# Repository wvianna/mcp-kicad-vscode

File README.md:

# KiCAD MCP para VS Code — mcp-kicad-vscode

Workspace que combina um **servidor MCP para automação de design de PCB com KiCad** e o **projeto de hardware** (placa de circuito impresso) desenvolvido com ele.

- **`KiCAD-MCP-Server/`** — Servidor MCP (Node.js/TypeScript + Python) que permite que assistentes de IA controlem o KiCad: criação de esquemáticos, layout de PCB, roteamento, DRC, exportação e integração com catálogos de componentes.
- **`project-kicad/`** — Projeto KiCad real: placa **seguidor de linhas** de 4 camadas (`seguidor_de_linhas_4camada2-2026-1`), com 97 footprints e 83 nets.

## Visão geral

O objetivo deste workspace é usar IA assistida para projetar, validar e preparar o projeto da PCB para fabricação. O servidor expõe as operações do KiCad como *tools* MCP (233 registradas), permitindo que um agente abra projetos, posicione componentes, roteie trilhas, crie zonas, rode DRC e exporte arquivos de fabricação — com o [Model Context Protocol](https://modelcontextprotocol.io/) (spec 2025-06-18).

Principais características:

- **233 ferramentas MCP** em 16 categorias (esquemático, PCB, roteamento, regras/DRC, exportação, bibliotecas, JLCPCB/DigiKey, freerouting etc.);
- **Fluxo de trabalho completo de esquemático**: criação, edição em lote, hierarquia, netlist, ERC;
- **Design de PCB**: componentes, trilhas, vias, zonas/pours, clearances, DRC, fotos 2D;
- **Integração com fabricantes**: catálogo JLCPCB (2,5 M+ peças), datasheets via LCSC e busca DigiKey;
- **Autorouter Freerouting** integrado;
- **Suporte multiplataforma** (Linux, Windows, macOS);
- **Integração em tempo real com a UI do KiCad via IPC API** (experimental — exige `kicad-python`);
- Repositório upstream: [mixelpixx/KiCAD-MCP-Server](https://github.com/mixelpixx/KiCAD-MCP-Server) (detalhes completos no [README do servidor](KiCAD-MCP-Server/README.md)).

## Demonstração

Preview da placa do projeto:

Vídeo de preview da PCB (arquivo local — não incorporado diretamente):

[Preview da PCB seguidor de linhas](project-kicad/video/PREVIAPCBSEGUIDORLINHAS.mp4)

## Documentação acadêmica

Este workspace inclui dois documentos sobre o servidor MCP, de autoria de
**William da Silva Vianna (Instituto Federal Fluminense — IFF)**:

| Documento | PDF | Fontes LaTeX | Escopo |
|---|---|---|---|
| **Artigo** | [`artigo/artigo-mcp-kicad-vscode.pdf`](artigo/artigo-mcp-kicad-vscode.pdf) | [`artigo/`](artigo/) | 12 páginas: arquitetura, catálogo, resultados de teste, estudo de caso |
| **Monografia** | [`monografia/monografia-mcp-kicad-vscode.pdf`](monografia/monografia-mcp-kicad-vscode.pdf) | [`monografia/`](monografia/) | 56 páginas: detalhamento completo do MCP (arquitetura, 233 ferramentas, integrações, estudo de caso, apêndices) |

Os documentos citam apenas dados verificáveis do repositório. As evidências
(logs de teste de 10/09/2026 e relatório de DRC) estão em
[`evidencias/`](evidencias/); informações ausentes no workspace estão marcadas
explicitamente (ver [`monografia/MONOGRAFIA_PENDENCIAS.md`](monografia/MONOGRAFIA_PENDENCIAS.md)).

## Funcionalidades

### Servidor MCP (KiCAD-MCP-Server)

- [x] 233 tools MCP registradas + descoberta por palavra-chave (`search_tools`, `get_category_tools`)
- [x] Recursos dinâmicos (23) expondo o estado do projeto
- [x] Ferramentas de esquemático: componentes, wires, labels, hierarquia, ERC, netlist, sync PCB↔esquemático
- [x] Ferramentas de PCB: board, camadas, componentes, roteamento, vias, zonas, DRC, import/export
- [x] Criação de footprints e símbolos personalizados
- [x] Integração JLCPCB (busca local + API), datasheets LCSC e DigiKey
- [x] Roteador Freerouting (via Java, Docker ou Podman)
- [x] Suporte a importação de PCBs de fornecedores (PADS, Altium, Eagle, Allegro etc.)
- [ ] Backend IPC em tempo real — experimental, exige `kicad-python` (padrão atual local: SWIG)

### Projeto de hardware (project-kicad)

- [x] Placa 4 camadas (F.Cu, B.Cu, In1.Cu, In2.Cu) — 82,2 × 80,3 mm
- [x] 97 componentes (80 da lib `mylib`, sensores IR `ITR8307`, ESP32, ponte H, MPPT, USB-C — conforme nets e BOM)
- [x] 83 nets (GND, +5V, +3V3, VBAT e sinais `/mptt/*`, `/ponteH/*`, `/usb-c/*`, `/IO*`)
- [x] DRC executado via `kicad-cli` (10/09/2026): 11 violações residuais (9 erros + 2 avisos), **0 itens não conectados** — relatório em [`project-kicad/docs/drc-seguidor-de-linhas-2026-09-10.json`](project-kicad/docs/drc-seguidor-de-linhas-2026-09-10.json); correções pendentes antes da fabricação
- [x] `BOM.csv` e bibliotecas locais (`mylib/`, `logopcb/`)

## Arquitetura

```mermaid
flowchart LR
    A[Assistente de IA<br/>cliente MCP] -->|stdio| B[KiCAD-MCP-Server<br/>Node.js / TypeScript]
    B -->|comandos JSON| C[python/kicad_interface.py<br/>SWIG pcbnew]
    B -.->|IPC opcional| D[KiCad IPC API<br/>exige kicad-python]
    C --> E[Arquivos .kicad_pro/.kicad_pcb/.kicad_sch]
    D --> E
    E --> F[project-kicad/<br/>seguidor_de_linhas_4camada2-2026-1]
    C --> G[kicad-cli<br/>DRC / exportações]
```

Fluxo: o agente de IA envia chamadas de ferramenta ao servidor Node; o servidor despacha para o processo Python que opera o KiCad via `pcbnew` (SWIG) — ou pela IPC API quando disponível — e os resultados refletem nos arquivos do projeto KiCad.

## Estrutura do projeto

```text
mcp-kicad-vscode/
├── KiCAD-MCP-Server/          # Servidor MCP (repo aninhado, upstream mixelpixx)
│   ├── src/                   # TypeScript — servidor e 233 tools
│   ├── python/                # Interface pcbnew (SWIG) / IPC
│   ├── tests/                 # testes pytest (test_*.py)
│   ├── tests-ts/              # testes Vitest (*.test.ts)
│   ├── config/                # exemplos de configuração de clientes MCP
│   ├── docs/                  # documentação detalhada do servidor
│   ├── package.json           # scripts de build/test/lint
│   ├── pyproject.toml         # Black/Isort/MyPy
│   └── run-kicad-mcp.sh       # launcher com env do KiCad (snap)
├── project-kicad/             # Projeto de hardware (PCB)
│   ├── seguidor_de_linhas_4camada2-2026-1.kicad_pro/.kicad_pcb/.kicad_sch
│   ├── mylib/                 # bibliotecas de footprints locais
│   ├── imagens/               # imagens da placa
│   ├── video/                 # vídeo de preview
│   ├── docs/                  # PDF do esquemático e listagens
│   └── BOM.csv
├── docs/                      # guias de setup local (pt-BR)
└── .gitignore
```

## Requisitos

### Software

| Ferramenta | Versão | Observação |
|---|---|---|
| Node.js | ≥ 20 | usado no CI (20.x/22.x) |
| TypeScript | 5.9 | compilação via `npm run build` |
| npm | — | gerenciador de dependências |
| Python | ≥ 3.9 | local: 3.12.3 (`.venv`) |
| KiCad | 9.0.7 | instalação **snap** (`/snap/kicad/22`) |
| JRE | 21 | apenas para suítes de teste do Freerouting (CI) |

Opcional: `kicad-python` (`pip install kicad-python`) habilita o backend IPC em tempo real; sem ele o servidor usa o backend SWIG.

### Hardware

- Para executar o servidor: computador com o KiCad instalado (o próprio KiCad é o "hardware").
- Projeto `project-kicad`: placa 4 camadas (ver [BOM.csv](project-kicad/BOM.csv) e [esquemático](project-kicad/docs/esquemático) para lista completa de componentes).

## Instalação

### 1. Clonar e preparar o servidor

```bash
cd KiCAD-MCP-Server
npm ci
npm run build
```

### 2. Ambiente Python

```bash
cd KiCAD-MCP-Server
python -m venv .venv
source .venv/bin/activate
pip install -r requirements.txt -r requirements-dev.txt
```

### 3. KiCad (snap) e habilitação da IPC API

Instale o KiCad 9 via snap e, no KiCad, habilite a API IPC em:

**Preferences → Plugins → Enable IPC API Server**

> Passo a passo completo de instalação local em [`docs/setup-mcp.txt`](docs/setup-mcp.txt).

## Configuração

### Variáveis de ambiente (opcional)

Copie [`.env.example`](KiCAD-MCP-Server/.env.example) para `.env` para habilitar integrações com JLCPCB e DigiKey:

```bash
cp KiCAD-MCP-Server/.env.example KiCAD-MCP-Server/.env
```

- `JLCPCB_APP_ID`, `JLCPCB_API_KEY`, `JLCPCB_API_SECRET` — API da JLCPCB (opcional; sem elas, a busca usa a base local);
- `DIGIKEY_CLIENT_ID`, `DIGIKEY_CLIENT_SECRET`, `DIGIKEY_LOCALE_*` — API DigiKey (opcional).

**Nunca commite o `.env`** — valores reais não devem aparecer em exemplos ou commits.

### Configuração do cliente MCP

Exemplos para diferentes clientes em `KiCAD-MCP-Server/config/`:

- `claude-desktop-config.json`, `opencode.json`, `vscode-mcp.example.json`
- `linux-config.example.json`, `macos-config.example.json`, `windows-config.example.json`

Variáveis de ambiente relevantes (definidas em `.vscode/mcp.json` — caminhos **máquina-específicos**, ajuste conforme sua instalação):

| Variável | Efeito |
|---|---|
| `KICAD_BACKEND=auto` | tenta IPC e cai para SWIG se `kicad-python` não estiver instalado |
| `KICAD_PYTHON` | caminho do interpretador Python do servidor (venv) |
| `PYTHONPATH` | `pcbnew` do KiCad (snap) |
| `LD_LIBRARY_PATH` | bibliotecas nativas do KiCad (snap) — obrigatório |
| `KICAD_AUTO_LAUNCH=false` | não abre o KiCad automaticamente |

## Uso

### Iniciar o servidor MCP

No VS Code: **Ctrl+Shift+P → `MCP: Start Server`** (usa `.vscode/mcp.json`).

Ou pelo terminal:

```bash
cd KiCAD-MCP-Server
./run-kicad-mcp.sh          # launcher com env do KiCad snap
# equivale a:
node dist/index.js          # sem env do KiCad: SWIG/headless
```

### Exemplos de fluxo com o assistente de IA

Com o servidor MCP ativo, um assistente pode, por exemplo:

1. `open_project` no `project-kicad/seguidor_de_linhas_4camada2-2026-1.kicad_pro`;
2. `get_board_info` / `get_component_list` para inspecionar a placa;
3. `run_drc` para validar regras de projeto;
4. `export_gerber` / `export_drill` para gerar arquivos de fabricação.

Todos os comandos de ferramentas MCP estão documentados em `KiCAD-MCP-Server/docs/TOOL_INVENTORY.md`.

### Trabalhando com o projeto KiCad

Abrir o projeto no KiCad e/ou validar DRC pela linha de comando (com o ambiente do snap exportado):

```bash
cd project-kicad
kicad-cli pcb drc --output /tmp/drc.json --format json seguidor_de_linhas_4camada2-2026-1.kicad_pcb
```

## Solução de problemas

| Sintoma | Causa provável | Solução |
|---|---|---|
| `ImportError: libwx_gtk3u_gl-3.2.so.0` | `LD_LIBRARY_PATH` ausente | Usar `./run-kicad-mcp.sh` ou exportar as variáveis do snap |
| `No module named 'pcbnew'` | `PYTHONPATH` errado | `export PYTHONPATH=/snap/kicad/22/usr/lib/python3/dist-packages` |
| Servidor em `backend: swig`, sem realtime | `kicad-python` não instalado | `pip install kicad-python` (ou aceitar SWIG) |
| `kicad-cli: error while loading shared libraries: libkicommon.so` | env do snap ausente | Exportar `LD_LIBRARY_PATH` antes do `kicad-cli` |
| DRC acusa clearance de zona | fill de zona desatualizado | Refill das zonas (tecla **B** no KiCad ou `pcbnew.ZONE_FILLER`) |
| `docs/TOOL_INVENTORY.md` desatualizado | tools adicionadas/removidas | `npm run docs:tools` |

## Desenvolvimento

```bash
cd KiCAD-MCP-Server

npm run build           # compilar TypeScript -> dist/
npm run dev             # watch + nodemon (redeployment automático)
npm run lint            # eslint src/ + black --check + mypy + flake8 (python/)
npm run format          # prettier 'src/**/*.ts' && black python/
npm run test            # vitest (tests-ts/) + pytest (tests/)
npm run test:ts         # somente testes TypeScript
npm run test:py         # somente testes Python
npm run test:coverage   # pytest com cobertura (pytest-cov)
npm run docs:tools      # regenerar docs/TOOL_INVENTORY.md
pre-commit run --all-files   # hooks de qualidade (git)
```

- **Testes**: Vitest (`tests-ts/*.test.ts`) e pytest (`tests/test_*.py`, `testpaths = tests`).
- **CI**: `.github/workflows/ci.yml` (matrix Node 20/22 e Python 3.9–3.12) — inclui gates de `docs:tools:check` e `lint:ts`.
- **Estilo (em `KiCAD-MCP-Server/`):** TypeScript estrito + Prettier/ESLint; Python Black (100 col) + Isort + MyPy + Flake8.

## Licença

- **KiCAD-MCP-Server:** MIT (ver [`LICENSE`](KiCAD-MCP-Server/LICENSE)).
- **Workspace/projeto raiz:** licença não identificada — nenhum arquivo `LICENSE` foi encontrado na raiz deste repositório.

## Créditos

- Servidor MCP: projeto upstream [KiCAD-MCP-Server](https://github.com/mixelpixx/KiCAD-MCP-Server) (autores originais conforme repositório; documentação detalhada em [`KiCAD-MCP-Server/README.md`](KiCAD-MCP-Server/README.md)).
- Projeto de hardware `seguidor_de_linhas_4camada2-2026-1`: o bloco de título do esquemático registra **"Autor: William / IFF"** (revisão `r01`), confirmando a autoria no próprio projeto.

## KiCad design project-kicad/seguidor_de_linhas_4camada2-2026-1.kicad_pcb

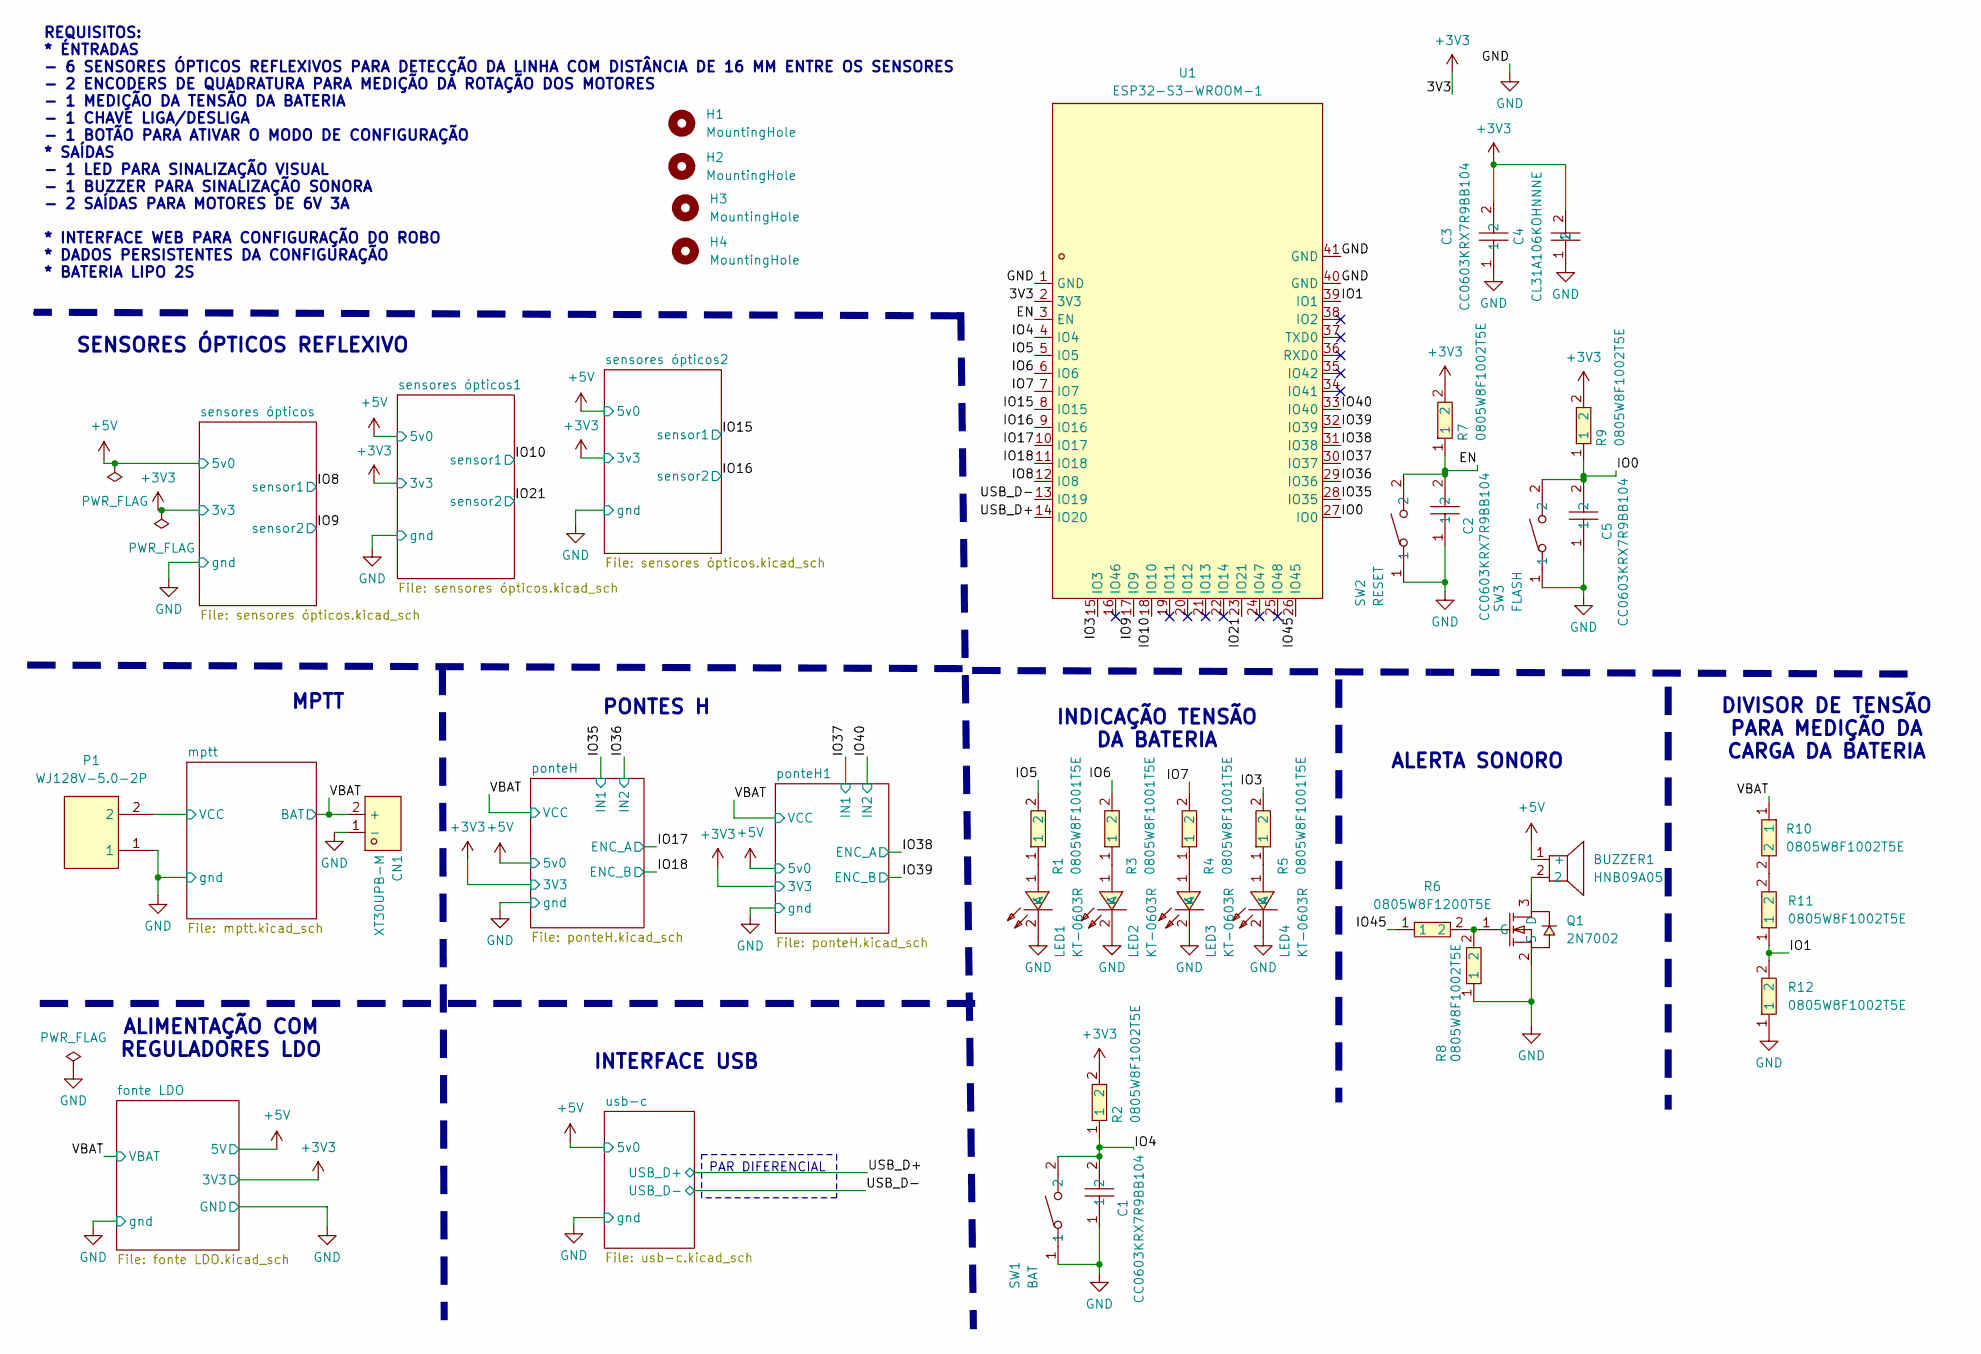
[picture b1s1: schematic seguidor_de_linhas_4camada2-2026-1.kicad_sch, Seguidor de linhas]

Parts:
BUZZER1: HNB09A05; BUZ-TH_BD9.6-P5.00-D0.7-FD; MPN HNB09A05; LCSC Part C96493
C1, C2, C3, C5: CC0603KRX7R9BB104; C0603; MPN CC0603KRX7R9BB104; LCSC Part C14663
C4: CL31A106KOHNNNE; C1206; MPN CL31A106KOHNNNE; LCSC Part C1849
CN1: XT30UPB-M; CONN-TH_XT30UPB-M; MPN XT30UPB-M; LCSC Part C428721
H1, H2, H3, H4: MountingHole; MountingHole_3.2mm_M3
LED1, LED2, LED3, LED4: KT-0603R; LED-SMD_L1.6-W0.8-R-RD; MPN KT-0603R; LCSC Part C2286
P1: WJ128V-5.0-2P; CONN-TH_2P-P5.00_WJ128V-5.0-2P; MPN WJ128V-5.0-02P-14-00A; LCSC Part C8269
Q1: 2N7002; SOT-23-3_L2.9-W1.3-P1.90-LS2.4-BR; MPN 2N7002; LCSC Part C8545
R1, R3, R4, R5: 0805W8F1001T5E; R0805; MPN 0805W8F1001T5E; LCSC Part C17513
R2, R7, R8, R9, R10, R11, R12: 0805W8F1002T5E; R0805; MPN 0805W8F1002T5E; LCSC Part C17414
R6: 0805W8F1200T5E; R0805; MPN 0805W8F1200T5E; LCSC Part C17437
SW1: BAT; SW-SMD_L3.9-W3.0-P4.45; MPN TS-1088-AR02016; LCSC Part C720477
SW2: RESET; SW-SMD_L3.9-W3.0-P4.45; MPN TS-1088-AR02016; LCSC Part C720477
SW3: FLASH; SW-SMD_L3.9-W3.0-P4.45; MPN TS-1088-AR02016; LCSC Part C720477
U1: ESP32-S3-WROOM-1; WIRELM-SMD_ESP32-S3-WROOM-1; MPN ESP32-S3-WROOM-1-N16R8; LCSC Part C2913202

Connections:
+3V3: C3.2, C4.2, R2.2, R7.2, R9.2, U1.2 (3V3); also elsewhere on the board
+5V: BUZZER1.1 (+); also elsewhere on the board
/EN: C2.2, R7.1, SW2.2, U1.3 (EN)
/IO0: C5.2, R9.1, SW3.2, U1.27 (IO0)
/IO1: R11.1, R12.2, U1.39 (IO1)
/IO3: R5.2, U1.15 (IO3)
/IO4: C1.2, R2.1, SW1.2, U1.4 (IO4)
/IO5: R1.2, U1.5 (IO5)
/IO6: R3.2, U1.6 (IO6)
/IO7: R4.2, U1.7 (IO7)
/IO8: U1.12 (IO8); also elsewhere on the board
/IO9: U1.17 (IO9); also elsewhere on the board
/IO10: U1.18 (IO10); also elsewhere on the board
/IO15: U1.8 (IO15); also elsewhere on the board
/IO16: U1.9 (IO16); also elsewhere on the board
/IO17: U1.10 (IO17); also elsewhere on the board
/IO18: U1.11 (IO18); also elsewhere on the board
/IO21: U1.23 (IO21); also elsewhere on the board
/IO35: U1.28 (IO35); also elsewhere on the board
/IO36: U1.29 (IO36); also elsewhere on the board
/IO37: U1.30 (IO37); also elsewhere on the board
/IO38: U1.31 (IO38); also elsewhere on the board
/IO39: U1.32 (IO39); also elsewhere on the board
/IO40: U1.33 (IO40); also elsewhere on the board
/IO45: R6.1, U1.26 (IO45)
/USB_D+: U1.14 (IO20); also elsewhere on the board
/USB_D-: U1.13 (IO19); also elsewhere on the board
/VBAT: CN1.2 (+), R10.1; also elsewhere on the board
/mptt/VCC: P1.2; also elsewhere on the board
GND: C1.1, C2.1, C3.1, C4.1, C5.1, CN1.1 (-), LED1.2 (K), LED2.2 (K), LED3.2 (K), LED4.2 (K), P1.1, Q1.2 (S), R8.1, R12.1, SW1.1, SW2.1, SW3.1, U1.1 (GND), U1.40 (GND), U1.41 (GND); also elsewhere on the board
unnamed: LED1.1 (A), R1.1
unnamed: LED2.1 (A), R3.1
unnamed: LED3.1 (A), R4.1
unnamed: LED4.1 (A), R5.1
unnamed: BUZZER1.2, Q1.3 (D)
unnamed: Q1.1 (G), R6.2, R8.2
unnamed: R10.2, R11.2

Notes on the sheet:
PONTES H
INTERFACE USB
INDICAÇÃO TENSÃO DA BATERIA
SENSORES ÓPTICOS REFLEXIVO
ALERTA SONORO
REQUISITOS: * ÉNTRADAS - 6 SENSORES ÓPTICOS REFLEXIVOS PARA DETECÇÃO DA LINHA COM DISTÂNCIA DE 16 MM ENTRE OS SENSORES - 2 ENCODERS DE QUADRATURA PARA MEDIÇÃO DA ROTAÇÃO DOS MOTORES - 1 MEDIÇÃO DA TENSÃO DA BATERIA - 1 CHAVE LIGA/DESLIGA - 1 BOTÃO PARA ATIVAR O MODO DE CONFIGURAÇÃO * SAÍDAS - 1 LED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
MPTT
DIVISOR DE TENSÃO PARA MEDIÇÃO DA CARGA DA BATERIA
ALIMENTAÇÃO COM REGULADORES LDO
PAR DIFERENCIAL

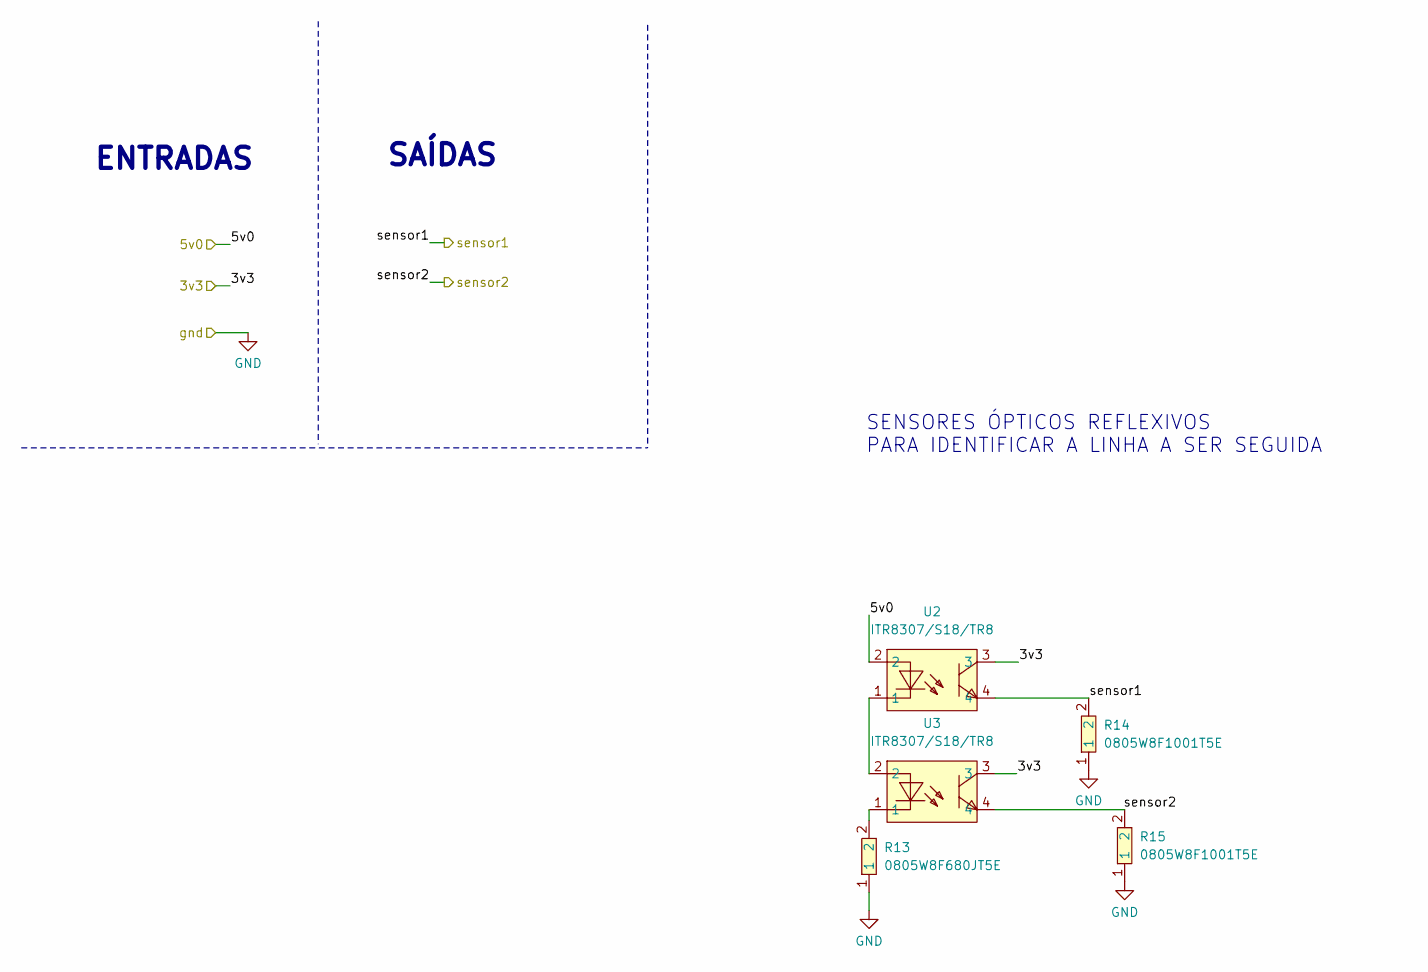
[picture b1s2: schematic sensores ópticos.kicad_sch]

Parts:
R13: 0805W8F680JT5E; R0805; MPN 0805W8F680JT5E; LCSC Part C17802
R14, R15: 0805W8F1001T5E; R0805; MPN 0805W8F1001T5E; LCSC Part C17513
U2, U3: ITR8307/S18/TR8; OPTO-SMD_ITR8307-S18-TR8-B; MPN ITR8307/S18/TR8(B); LCSC Part C115037

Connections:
+3V3: U2.3, U3.3; also elsewhere on the board
+5V: U2.2; also elsewhere on the board
/IO8: R14.2, U2.4; also elsewhere on the board
/IO9: R15.2, U3.4; also elsewhere on the board
GND: R13.1, R14.1, R15.1; also elsewhere on the board
unnamed: R13.2, U3.1
unnamed: U2.1, U3.2

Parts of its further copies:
R16, R19: 0805W8F680JT5E; R0805; MPN 0805W8F680JT5E; LCSC Part C17802
R17, R18, R20, R21: 0805W8F1001T5E; R0805; MPN 0805W8F1001T5E; LCSC Part C17513
U4, U5, U6, U7: ITR8307/S18/TR8; OPTO-SMD_ITR8307-S18-TR8-B; MPN ITR8307/S18/TR8(B); LCSC Part C115037

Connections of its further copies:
+3V3: U4.3, U5.3, U6.3, U7.3; also elsewhere on the board
+5V: U4.2, U6.2; also elsewhere on the board
/IO10: R17.2, U4.4; also elsewhere on the board
/IO15: R20.2, U6.4; also elsewhere on the board
/IO16: R21.2, U7.4; also elsewhere on the board
/IO21: R18.2, U5.4; also elsewhere on the board
GND: R16.1, R17.1, R18.1, R19.1, R20.1, R21.1; also elsewhere on the board
unnamed: R16.2, U5.1
unnamed: R19.2, U7.1
unnamed: U4.1, U5.2
unnamed: U6.1, U7.2

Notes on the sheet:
SENSORES ÓPTICOS REFLEXIVOS PARA IDENTIFICAR A LINHA A SER SEGUIDA
SAÍDAS
ENTRADAS

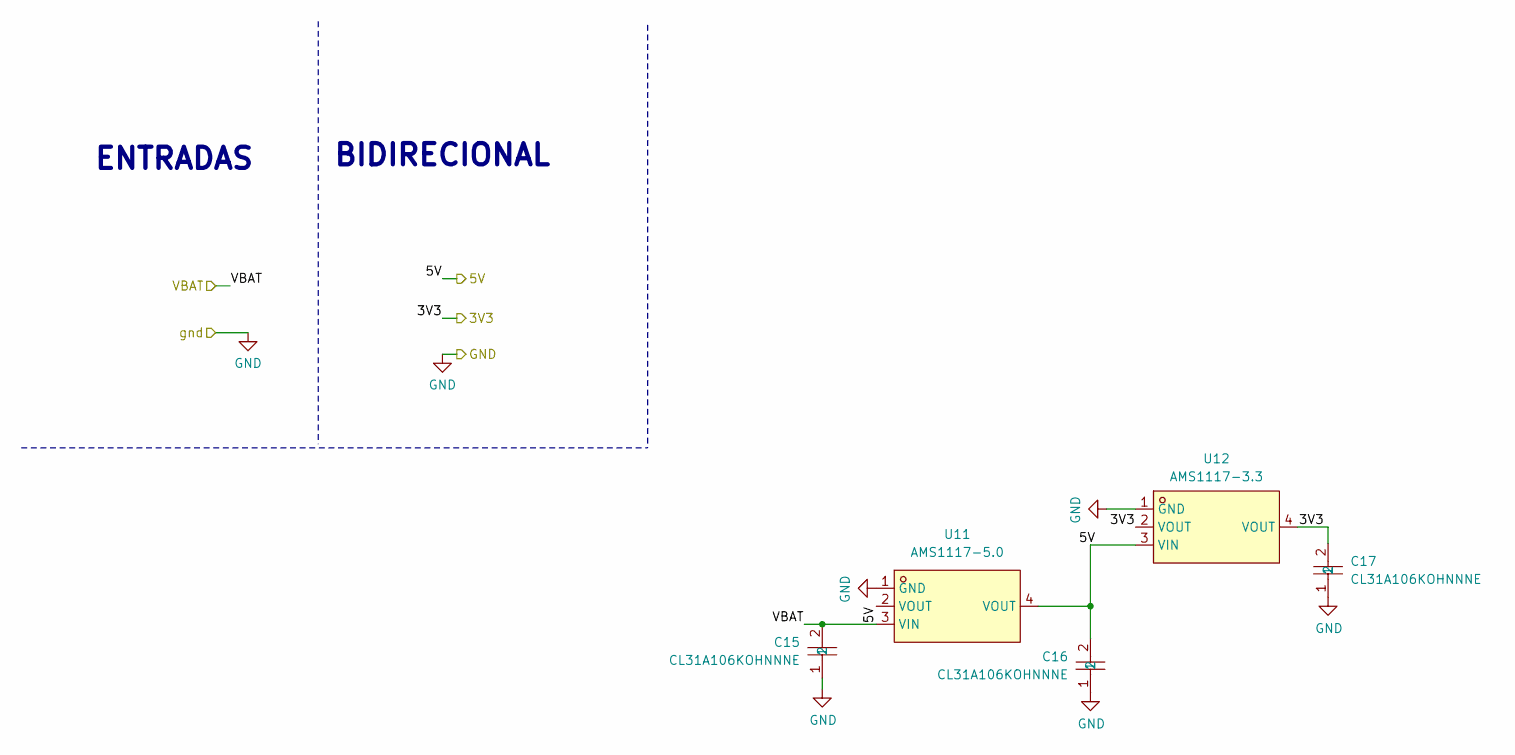
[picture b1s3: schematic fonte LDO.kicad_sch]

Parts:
C15, C16, C17: CL31A106KOHNNNE; C1206; MPN CL31A106KOHNNNE; LCSC Part C1849
U11: AMS1117-5.0; SOT-223_L6.5-W3.5-P2.30-LS7.0-BR; MPN AMS1117-5.0; LCSC Part C6187
U12: AMS1117-3.3; SOT-223-3_L6.5-W3.4-P2.30-LS7.0-BR; MPN AMS1117-3.3; LCSC Part C6186

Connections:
+3V3: C17.2, U12.2 (VOUT), U12.4 (VOUT); also elsewhere on the board
+5V: C16.2, U11.2 (VOUT), U11.4 (VOUT), U12.3 (VIN); also elsewhere on the board
/VBAT: C15.2, U11.3 (VIN); also elsewhere on the board
GND: C15.1, C16.1, C17.1, U11.1 (GND), U12.1 (GND); also elsewhere on the board

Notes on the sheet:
BIDIRECIONAL
ENTRADAS

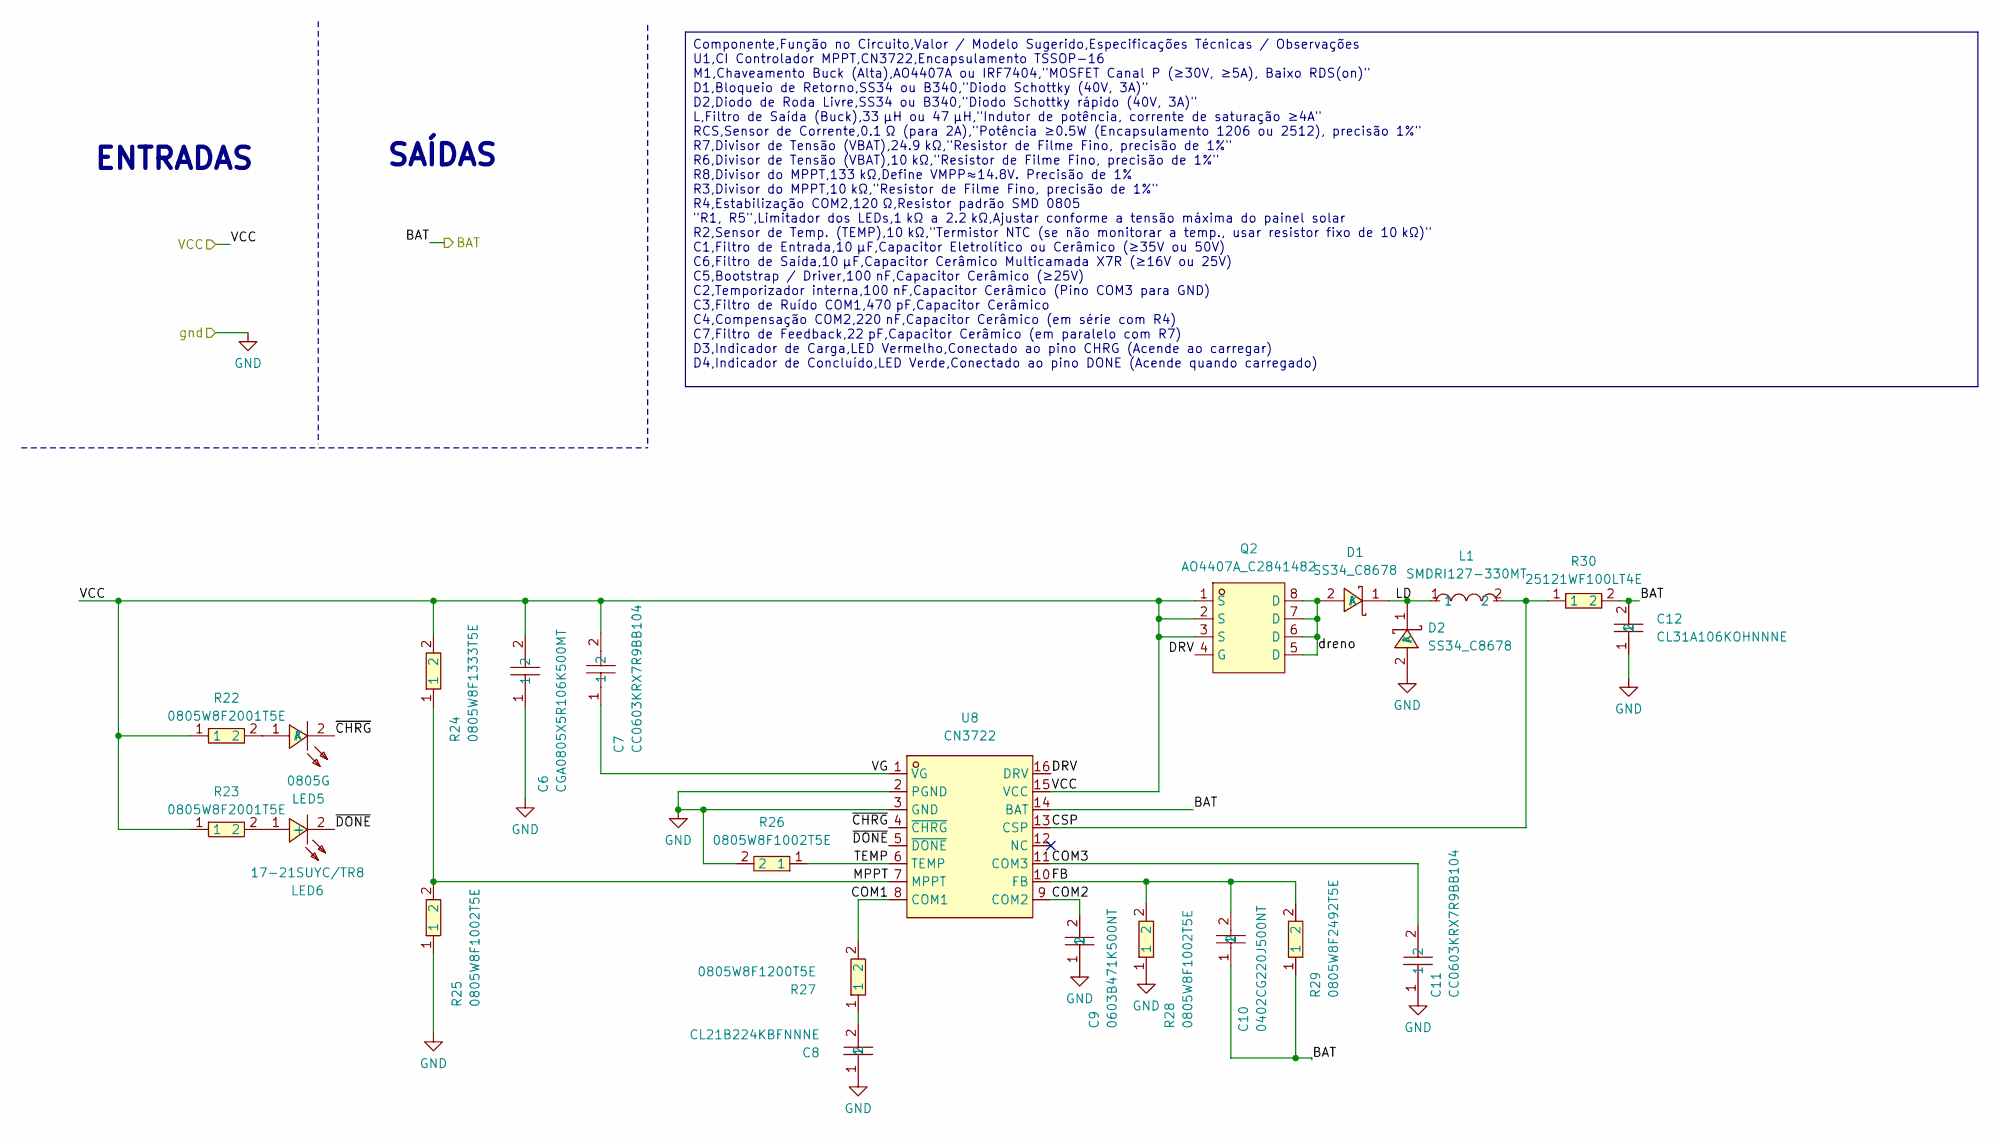
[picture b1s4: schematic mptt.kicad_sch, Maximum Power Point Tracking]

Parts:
C6: CGA0805X5R106K500MT; C0805; MPN CGA0805X5R106K500MT; LCSC Part C6119889
C7, C11: CC0603KRX7R9BB104; C0603; MPN CC0603KRX7R9BB104; LCSC Part C14663
C8: CL21B224KBFNNNE; C0805; MPN CL21B224KBFNNNE; LCSC Part C5378
C9: 0603B471K500NT; C0603; MPN 0603B471K500NT; LCSC Part C1620
C10: 0402CG220J500NT; C0402; MPN 0402CG220J500NT; LCSC Part C1555
C12: CL31A106KOHNNNE; C1206; MPN CL31A106KOHNNNE; LCSC Part C1849
D1, D2: SS34_C8678; SMA_L4.3-W2.6-LS5.2-RD; MPN SS34; LCSC Part C8678
L1: SMDRI127-330MT; IND-SMD_L12.3-W12.3; MPN SMDRI127-330MT; LCSC Part C9400
LED5: 0805G; LED0805-R-RD; MPN KT-0805G; LCSC Part C2297
LED6: 17-21SUYC/TR8; LED0805-R-RD; MPN KT-0805黄灯; LCSC Part C2296
Q2: AO4407A_C2841482; SOP-8_L5.0-W4.0-P1.27-LS6.0-BL; MPN AO4407A; LCSC Part C2841482
R22, R23: 0805W8F2001T5E; R0805; MPN 0805W8F2001T5E; LCSC Part C17604
R24: 0805W8F1333T5E; R0805; MPN 0805W8F1333T5E; LCSC Part C17452
R25, R26, R28: 0805W8F1002T5E; R0805; MPN 0805W8F1002T5E; LCSC Part C17414
R27: 0805W8F1200T5E; R0805; MPN 0805W8F1200T5E; LCSC Part C17437
R29: 0805W8F2492T5E; R0805; MPN 0805W8F2492T5E; LCSC Part C17571
R30: 25121WF100LT4E; R2512; MPN 25121WF100LT4E; LCSC Part C25466
U8: CN3722; TSSOP-16_L5.0-W4.4-P0.65-LS6.4-BL; MPN CN3722; LCSC Part C77905

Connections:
/VBAT: C10.1, C12.2, R29.1, R30.2, U8.14 (BAT); also elsewhere on the board
/mptt/COM1: R27.2, U8.8 (COM1)
/mptt/COM2: C9.2, U8.9 (COM2)
/mptt/COM3: C11.2, U8.11 (COM3)
/mptt/CSP: L1.2, R30.1, U8.13 (CSP)
/mptt/DRV: Q2.4 (G), U8.16 (DRV)
/mptt/FB: C10.2, R28.2, R29.2, U8.10 (FB)
/mptt/LD: D1.1 (K), D2.1 (K), L1.1
/mptt/MPPT: R24.1, R25.2, U8.7 (MPPT)
/mptt/TEMP: R26.1, U8.6 (TEMP)
/mptt/VCC: C6.2, C7.2, Q2.1 (S), Q2.2 (S), Q2.3 (S), R22.1, R23.1, R24.2, U8.15 (VCC); also elsewhere on the board
/mptt/VG: C7.1, U8.1 (VG)
/mptt/dreno: D1.2 (A), Q2.5 (D), Q2.6 (D), Q2.7 (D), Q2.8 (D)
/mptt/~CHRG: LED5.2 (K), U8.4 (~CHRG)
/mptt/~DONE: LED6.2 (-), U8.5 (~DONE)
GND: C6.1, C8.1, C9.1, C11.1, C12.1, D2.2 (A), R25.1, R26.2, R28.1, U8.2 (PGND), U8.3 (GND); also elsewhere on the board
unnamed: C8.2, R27.1
unnamed: LED5.1 (A), R22.2
unnamed: LED6.1 (+), R23.2

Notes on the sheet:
SAÍDAS
ENTRADAS
Componente,Função no Circuito,Valor / Modelo Sugerido,Especificações Técnicas / Observações U1,CI Controlador MPPT,CN3722,Encapsulamento TSSOP-16 M1,Chaveamento Buck (Alta),AO4407A ou IRF7404,"MOSFET Canal P (≥30V, ≥5A), Baixo RDS(on)​" D1,Bloqueio de Retorno,SS34 ou B340,"Diodo Schottky (40V, 3A)"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

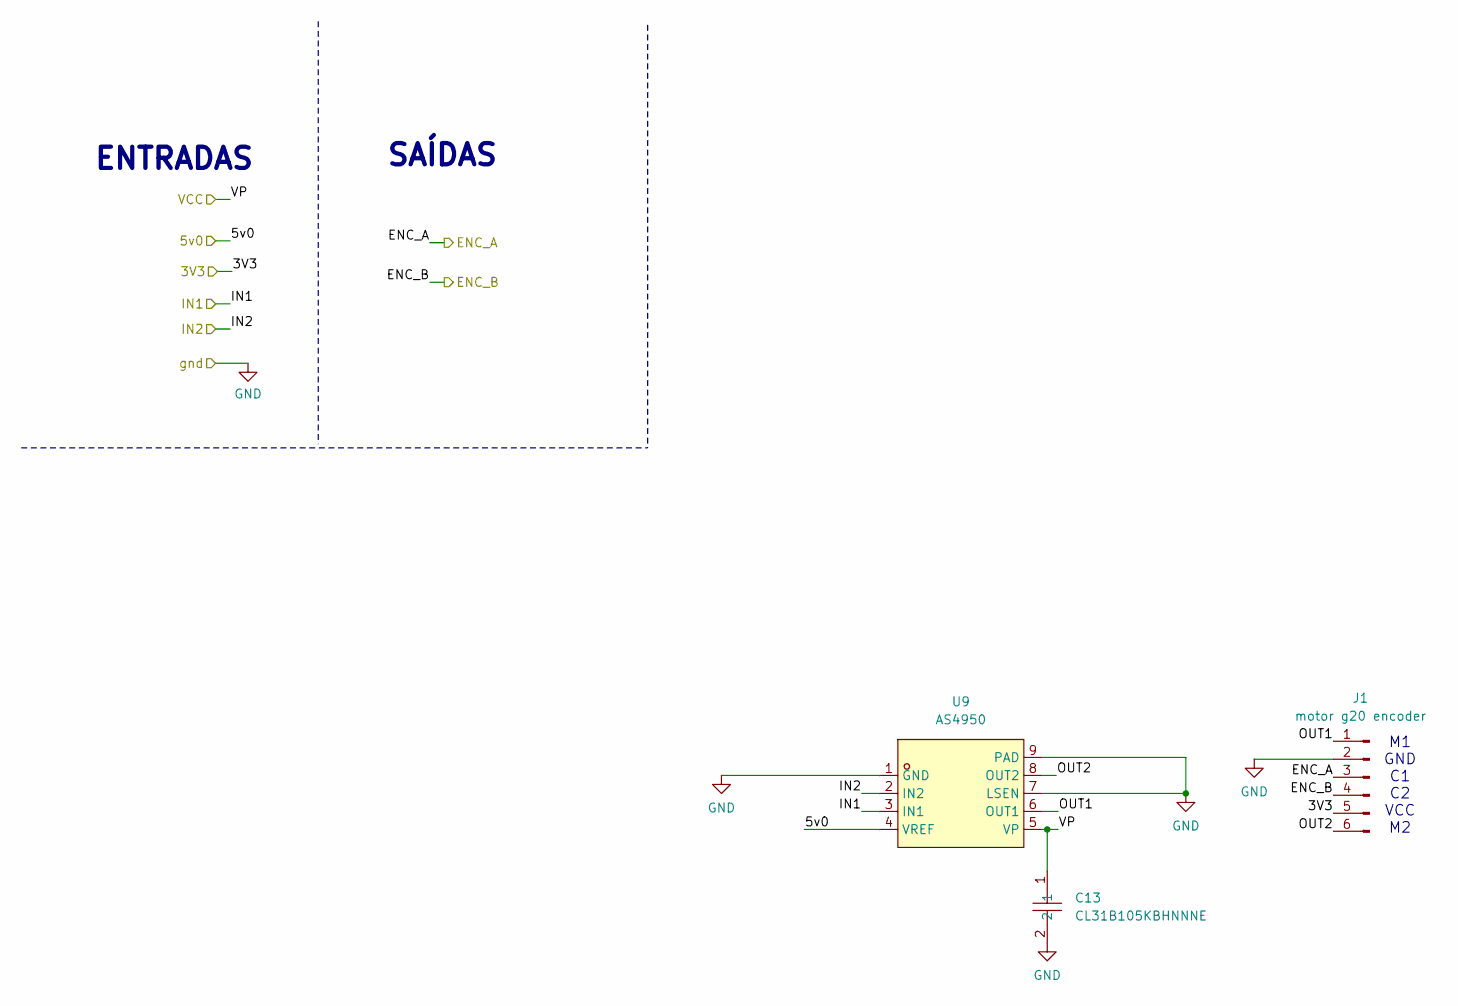
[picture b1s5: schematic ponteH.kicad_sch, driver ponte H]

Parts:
C13: CL31B105KBHNNNE; C1206; MPN CL31B105KBHNNNE; LCSC Part C1848
J1: motor g20 encoder; PinHeader_1x06_P2.54mm_Vertical
U9: AS4950; ESOP-8_L4.9-W3.9-P1.27-LS6.0-BL-EP; MPN AS4950; LCSC Part C2929412

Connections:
+3V3: J1.5; also elsewhere on the board
+5V: U9.4 (VREF); also elsewhere on the board
/IO17: J1.3; also elsewhere on the board
/IO18: J1.4; also elsewhere on the board
/IO35: U9.3 (IN1); also elsewhere on the board
/IO36: U9.2 (IN2); also elsewhere on the board
/VBAT: C13.1, U9.5 (VP); also elsewhere on the board
/ponteH/OUT1: J1.1, U9.6 (OUT1)
/ponteH/OUT2: J1.6, U9.8 (OUT2)
GND: C13.2, J1.2, U9.1 (GND), U9.7 (LSEN), U9.9 (PAD); also elsewhere on the board

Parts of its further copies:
C14: CL31B105KBHNNNE; C1206; MPN CL31B105KBHNNNE; LCSC Part C1848
J2: motor g20 encoder; PinHeader_1x06_P2.54mm_Vertical
U10: AS4950; ESOP-8_L4.9-W3.9-P1.27-LS6.0-BL-EP; MPN AS4950; LCSC Part C2929412

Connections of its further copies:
+3V3: J2.5; also elsewhere on the board
+5V: U10.4 (VREF); also elsewhere on the board
/IO37: U10.3 (IN1); also elsewhere on the board
/IO38: J2.3; also elsewhere on the board
/IO39: J2.4; also elsewhere on the board
/IO40: U10.2 (IN2); also elsewhere on the board
/VBAT: C14.1, U10.5 (VP); also elsewhere on the board
/ponteH1/OUT1: J2.1, U10.6 (OUT1)
/ponteH1/OUT2: J2.6, U10.8 (OUT2)
GND: C14.2, J2.2, U10.1 (GND), U10.7 (LSEN), U10.9 (PAD); also elsewhere on the board

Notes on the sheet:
SAÍDAS
ENTRADAS
M1 GND C1 C2 VCC M2

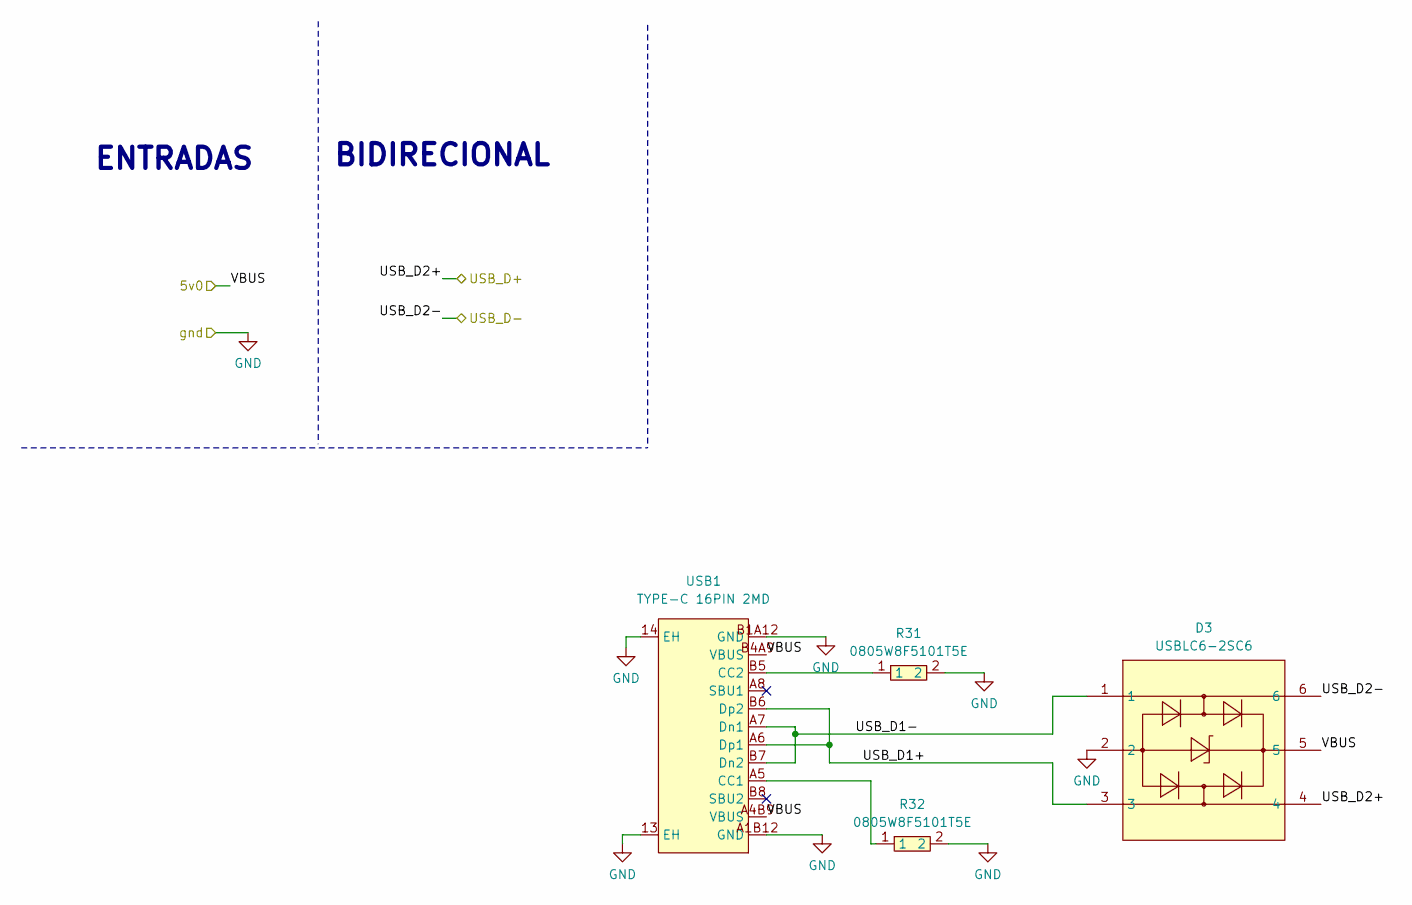
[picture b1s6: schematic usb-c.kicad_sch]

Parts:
D3: USBLC6-2SC6; SOT-23-6_L2.9-W1.6-P0.95-LS2.8-BL; MPN USBLC6-2SC6; LCSC Part C7519
R31, R32: 0805W8F5101T5E; R0805; MPN 0805W8F5101T5E; LCSC Part C27834
USB1: TYPE-C 16PIN 2MD; USB-C-SMD_TYPE-C-16PIN-2MD-073; MPN TYPE-C 16PIN 2MD(073); LCSC Part C2765186

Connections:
+5V: D3.5, USB1.A4B9 (VBUS), USB1.B4A9 (VBUS); also elsewhere on the board
/USB_D+: D3.4; also elsewhere on the board
/USB_D-: D3.6; also elsewhere on the board
/usb-c/USB_D1+: D3.3, USB1.A6 (Dp1), USB1.B6 (Dp2)
/usb-c/USB_D1-: D3.1, USB1.A7 (Dn1), USB1.B7 (Dn2)
GND: D3.2, R31.2, R32.2, USB1.13 (EH), USB1.14 (EH), USB1.A1B12 (GND), USB1.B1A12 (GND); also elsewhere on the board
unnamed: R32.1, USB1.A5 (CC1)
unnamed: R31.1, USB1.B5 (CC2)

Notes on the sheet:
BIDIRECIONAL
ENTRADAS
